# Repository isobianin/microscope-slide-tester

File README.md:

# Microscope slide tester

This is a small project done in collaboration with [Igor Kraev](https://uk.linkedin.com/in/igor-kraev-78a55821) from the Open University Microscope Suite. The device at hand is a simple continuity tester which is equipped with
a battery holder and can be recharged.

The protocol of operation:

1. Take the electrode lid off.

2. Clean your electrodes with either distilled water, acetone or IPA to remove any dust particles.

3. Press the slide against the electrodes. **If the front LED lights up, the side that is in contact with electrodes is conductive**.

4. Mark the conductive side.

5. Repeat steps 1-4 for as many slides as needed.

6. When done, close the electrode lid.

The tester can be operated while being charged

# Recharging and safety

The tester can be recharged from any USB port (5V). That includes a PC, a laptop or even a phone charger. In the baseline version, USB B is installed at the back of the teste. It
can be swapped for any other convenient connector. USB A to USB B is a quite common cable and can be found in lots of printers, scanners, in electronic workshops, etc.

There are no specific regulations for the battery charging. When the tester is being charged, an indicator in the back lights up. A so-called **"trickle charge"** technique is used to 
charge the batteries. It means that the duration of charging is extremely long (tens of hours) but you cannot overcharge the batteries. 

A suggested protocol of recharging is to charge the device while you are at your workplace and avoid leaving it charging for days and days for safety measures.

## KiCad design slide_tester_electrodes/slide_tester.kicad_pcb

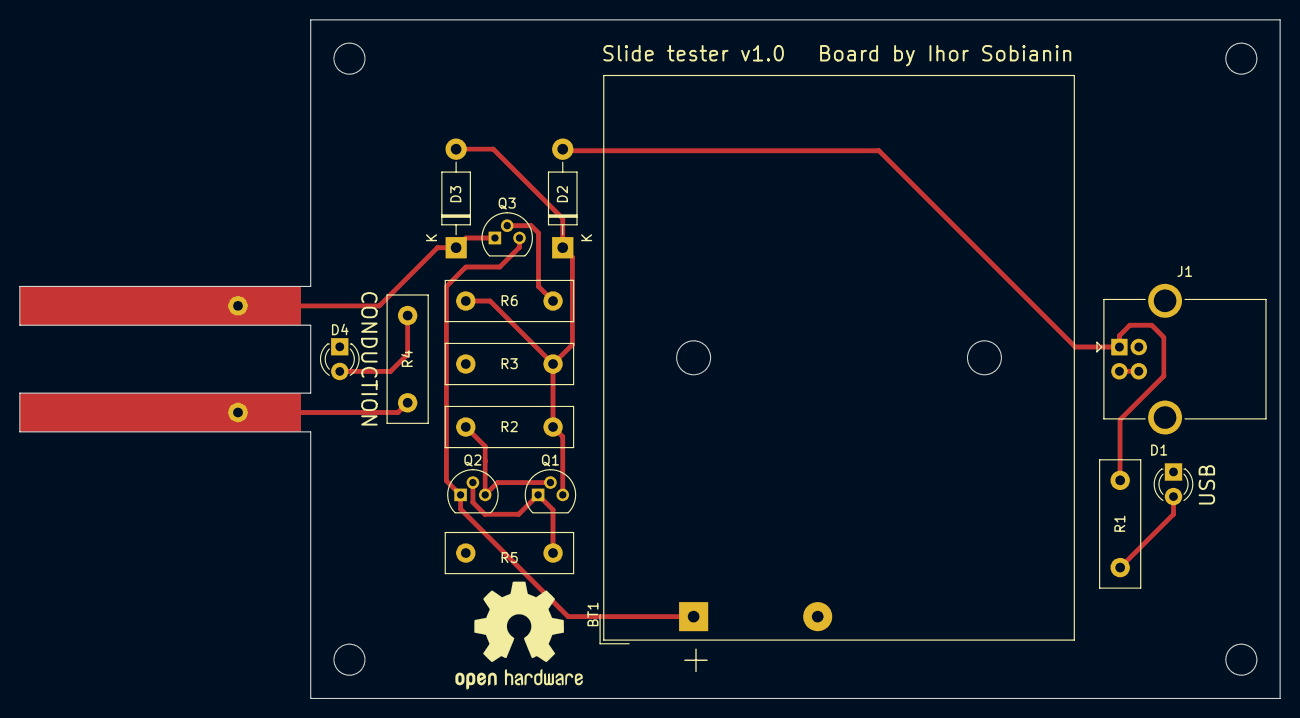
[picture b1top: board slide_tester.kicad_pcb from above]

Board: 2 copper layers, 130.0 x 70.0 mm, 17 parts (0 on the bottom side), 12 nets.

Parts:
BT1: Battery_Cell; BatteryHolder_TruPower_BH-331P_3xAA
D1, D4: LED; LED_D3.0mm
D2, D3: 1N4007; D_DO-41_SOD81_P10.16mm_Horizontal
J1: USB_A_Stacked; USB_B_OST_USB-B1HSxx_Horizontal
J2, J3: Conn_01x01_Male; electrode_pad
Q1, Q2, Q3: C32725; TO-92
R1: 560; R_Box_L13.0mm_W4.0mm_P9.00mm
R2: 12; R_Box_L13.0mm_W4.0mm_P9.00mm
R3: 10k; R_Box_L13.0mm_W4.0mm_P9.00mm
R4: 100; R_Box_L13.0mm_W4.0mm_P9.00mm
R5: 680; R_Box_L13.0mm_W4.0mm_P9.00mm
R6: 22k; R_Box_L13.0mm_W4.0mm_P9.00mm

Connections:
GND: BT1.2 (-), D1.1 (K), D4.1 (K), J1.4 (GND), J1.5 (Shield), R3.2, R5.2
unnamed: BT1.1 (+), Q2.1 (C), Q3.3 (E)
unnamed: D1.2 (A), R1.2
unnamed: D2.1 (K), D3.2 (A), Q1.3 (E), R2.1, R3.1, R6.1
unnamed: D2.2 (A), J1.1 (VBUS), R1.1
unnamed: D3.1 (K), J2.1, Q3.1 (C)
unnamed: D4.2 (A), R4.2
unnamed: J1.2 (D-), J1.3 (D+)
unnamed: J3.1, R4.1
unnamed: Q1.1 (C), Q2.2 (B), R5.1
unnamed: Q1.2 (B), Q2.3 (E), R2.2
unnamed: Q3.2 (B), R6.2

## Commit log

2023-10-27 Initial commit
    -create repo
    -add files
2023-10-27 Add enclosure
    Add FreeCAD enclosure files and STLs
2023-10-28 Add description, correct STL files
    Add readme-s
    Add figures
    Reorginise repo
2023-10-28 Add description, figures
    Add gitignore and delete back-ups
2023-10-28 Setup gitignore rules
2023-10-28 Update README.md
    Update Ohm sign ($\Omega$) to show correctly in-lines
2023-10-28 Update FreeCAD files
2023-11-02 Add photos
    Add photos of the tester
